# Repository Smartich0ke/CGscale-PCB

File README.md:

# CGscale-PCB
PCB designs for CG scale based on @Olkal 's design.

Note that some files are labelled as `robotcontrol` but they are the same thing, I just accidently nmaed it after another project I was working on.

##
The schematics have been exported as PDF (`robotcontrol.pdf`) but if you want to view the full project, You will need to open the .pro file with KiCad EDA .
##

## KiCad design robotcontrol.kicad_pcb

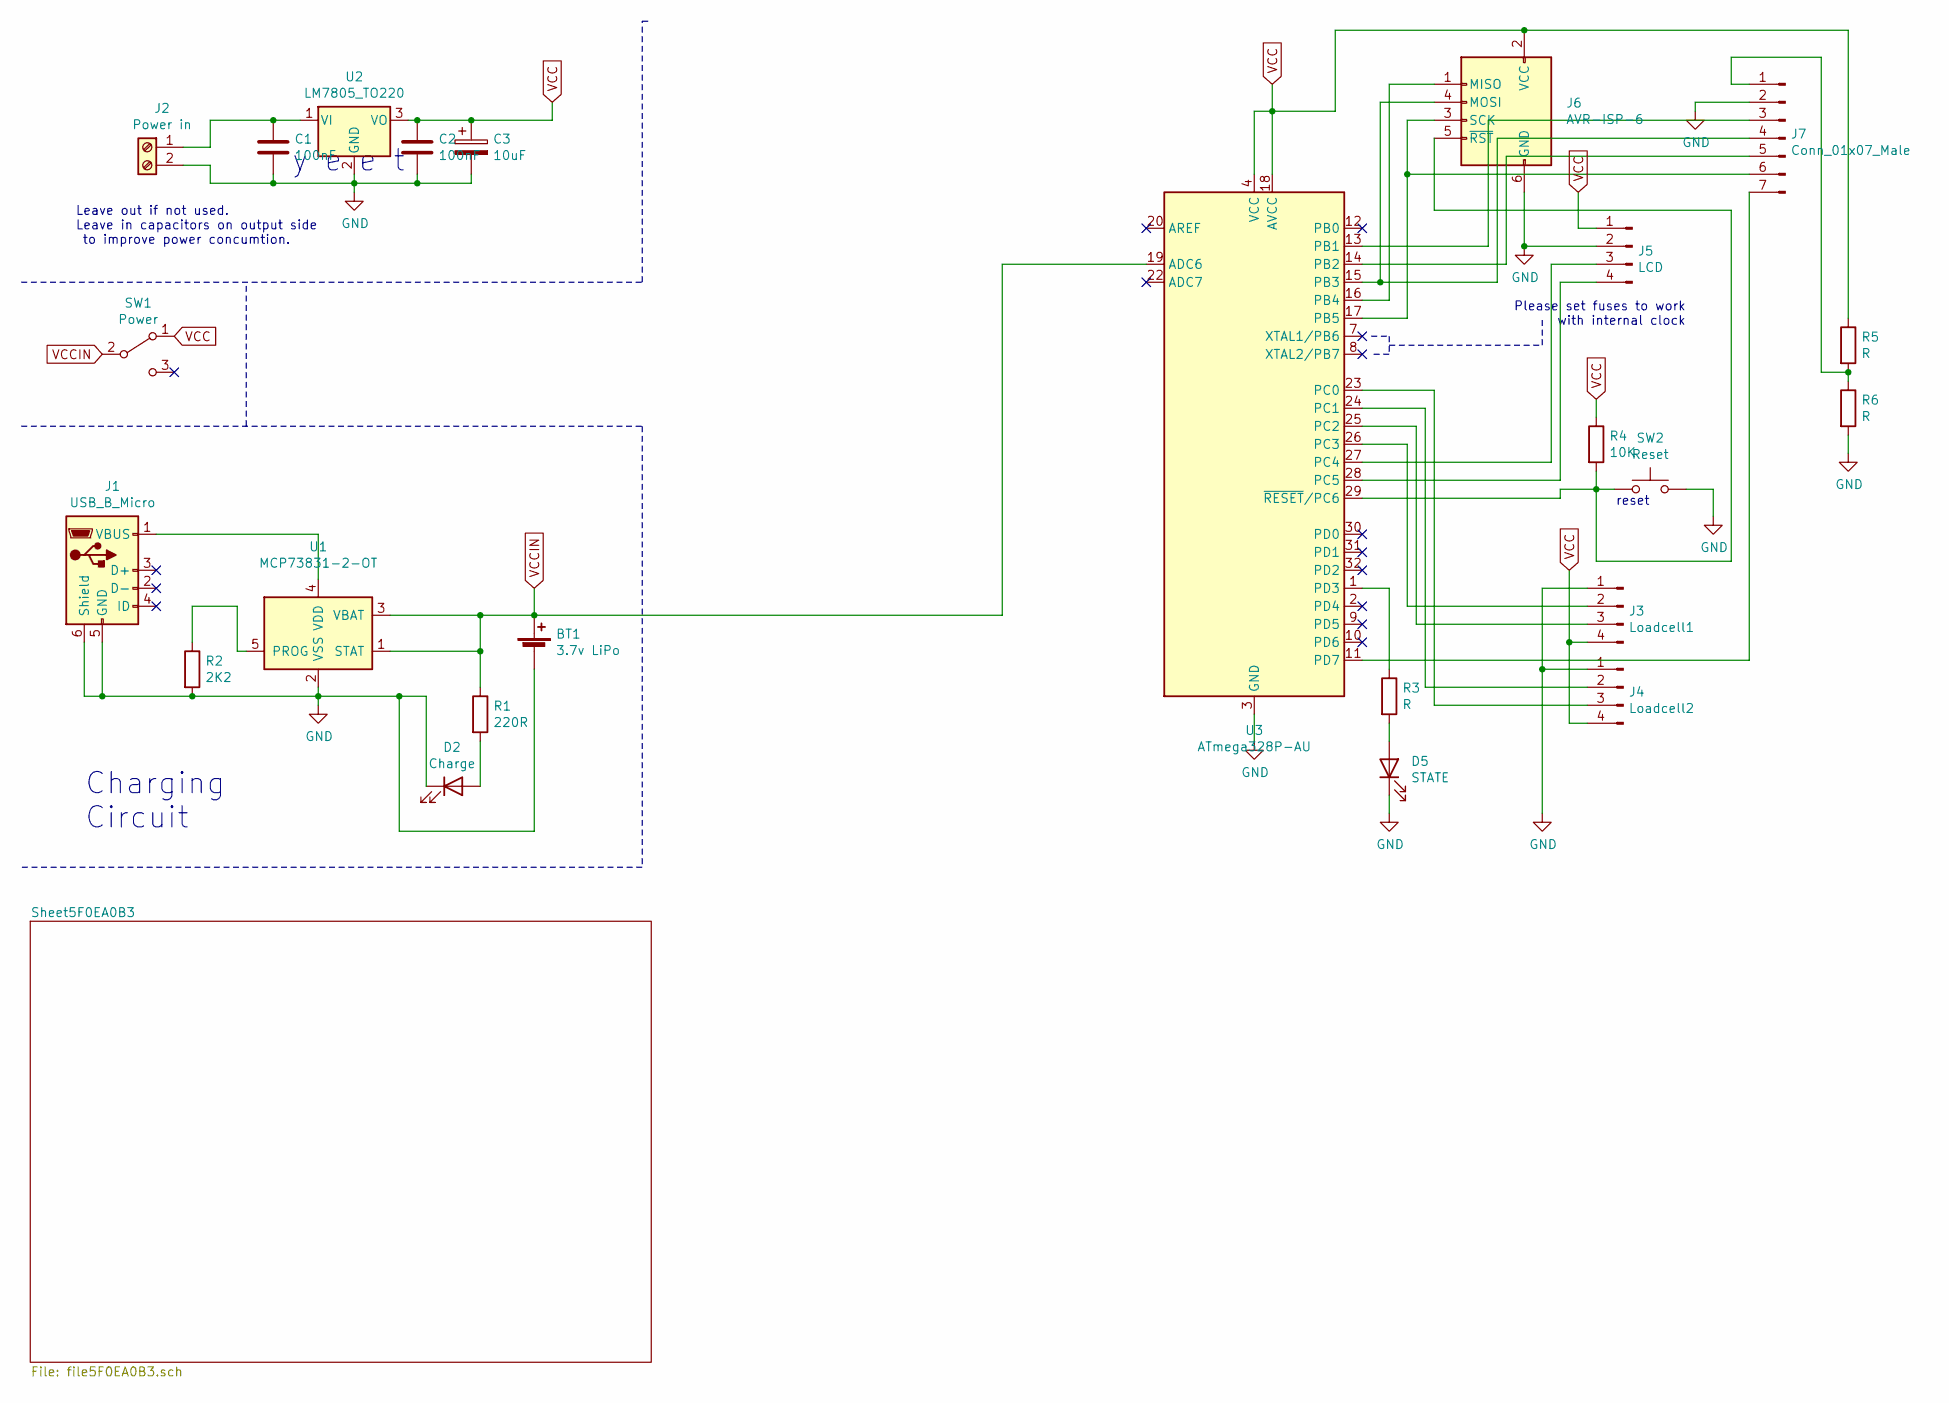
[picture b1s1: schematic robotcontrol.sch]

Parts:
BT1: 3.7v LiPo; TerminalBlock_bornier-2_P5.08mm
C1, C2: 100nF; C_Disc_D4.7mm_W2.5mm_P5.00mm
C3: 10uF; CP_Radial_D5.0mm_P2.50mm
D2: Charge; LED_D3.0mm
D5: STATE; LED_D3.0mm
J1: USB_B_Micro; USB_Micro-B_Wuerth_629105150521_CircularHoles
J2: Power in; PinHeader_1x07_P2.54mm_Vertical
J3: Loadcell1; PinHeader_1x04_P2.54mm_Vertical
J4: Loadcell2; PinHeader_1x04_P2.54mm_Vertical
J5: LCD; PinHeader_1x04_P2.54mm_Vertical
J6: AVR-ISP-6; PinHeader_2x03_P2.54mm_Vertical
J7: Conn_01x07_Male; PinHeader_1x07_P2.54mm_Vertical
R1: 220R; R_Axial_DIN0207_L6.3mm_D2.5mm_P10.16mm_Horizontal
R2: 2K2; R_Axial_DIN0207_L6.3mm_D2.5mm_P10.16mm_Horizontal
R3, R5, R6: R; R_Axial_DIN0207_L6.3mm_D2.5mm_P10.16mm_Horizontal
R4: 10K; R_Axial_DIN0207_L6.3mm_D2.5mm_P10.16mm_Horizontal
SW1: Power; PinHeader_1x03_P2.54mm_Vertical
SW2: Reset; SW_PUSH_6mm
U1: MCP73831-2-OT; SOT-23-5
U2: LM7805_TO220; TO-220-3_Vertical
U3: ATmega328P-AU; TQFP-32_7x7mm_P0.8mm

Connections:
GND: BT1.2 (-), C1.2, C2.2, C3.2, D2.1 (K), D5.1 (K), J1.5 (GND), J1.6 (Shield), J2.2, J3.1, J4.1, J5.2, J6.6 (GND), J7.2, R2.2, R6.2, SW2.2, U1.2 (VSS), U2.2 (GND), U3.3 (GND), U3.5 (GND), U3.21 (GND)
unnamed: C1.1, J2.1, U2.1 (VI)
unnamed: D2.2 (A), R1.2
unnamed: D5.2 (A), R3.2
unnamed: J1.1 (VBUS), U1.4 (VDD)
unnamed: J3.2, U3.26 (PC3)
unnamed: J3.3, U3.25 (PC2)
unnamed: J4.2, U3.24 (PC1)
unnamed: J4.3, U3.23 (PC0)
unnamed: J5.3, U3.27 (PC4)
unnamed: J5.4, U3.28 (PC5)
unnamed: J6.1 (MISO), U3.16 (PB4)
unnamed: J6.3 (SCK), J7.6, U3.17 (PB5)
unnamed: J6.4 (MOSI), J7.4, U3.15 (PB3)
unnamed: J6.5 (~RST), R4.2, SW2.1, U3.29 (~RESET~/PC6)
unnamed: J7.1, R5.2, R6.1
unnamed: J7.3, U3.13 (PB1)
unnamed: J7.5, U3.14 (PB2)
unnamed: J7.7, U3.11 (PD7)
unnamed: R2.1, U1.5 (PROG)
unnamed: R3.1, U3.1 (PD3)
VCC: C2.1, C3.1, J3.4, J4.4, J5.1, J6.2 (VCC), R4.1, R5.1, SW1.1 (A), U2.3 (VO), U3.4 (VCC), U3.6 (VCC), U3.18 (AVCC)
VCCIN: BT1.1 (+), R1.1, SW1.2 (B), U1.1 (STAT), U1.3 (VBAT), U3.19 (ADC6)

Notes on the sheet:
Leave out if not used. Leave in capacitors on output side to improve power concumtion.
y e e t
Charging Circuit
reset
Please set fuses to work with internal clock

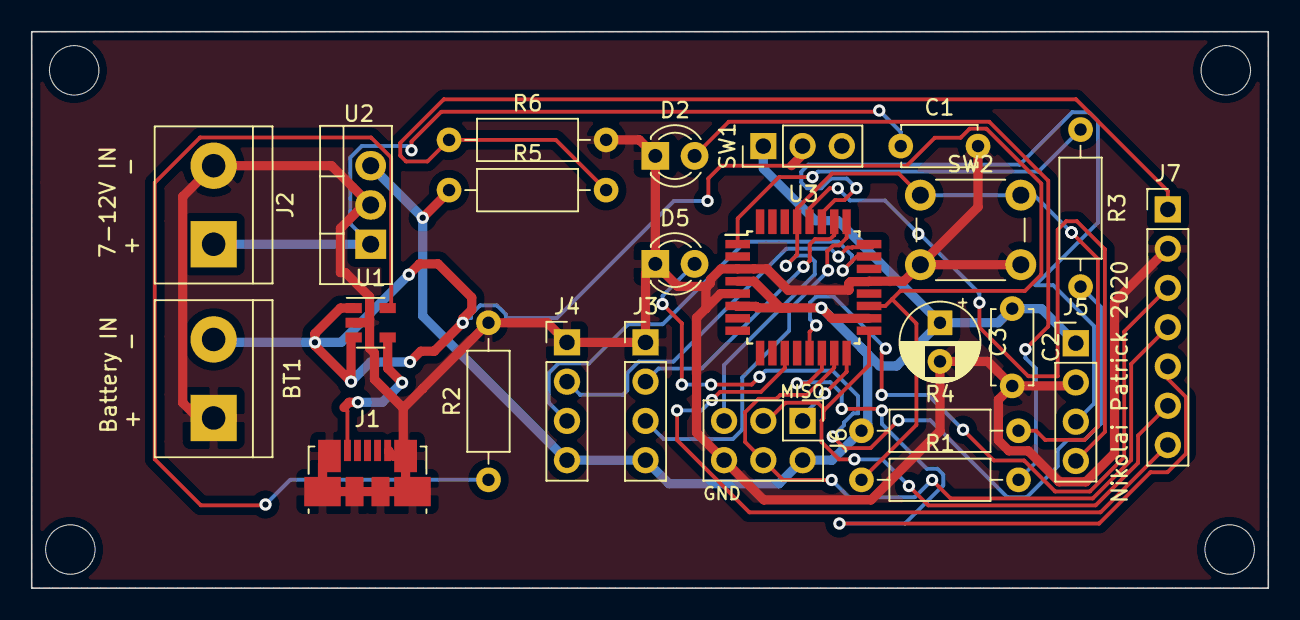
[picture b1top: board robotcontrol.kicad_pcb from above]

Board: 2 copper layers, 80.0 x 36.0 mm, 24 parts (0 on the bottom side), 23 nets.

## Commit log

2021-04-20 Add board files
2021-04-20 Specify what EDA is used
2021-04-20 Add PDF version of schematic
2021-04-20 Specify which EDA
